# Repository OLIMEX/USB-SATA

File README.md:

# USB-SATA
USB to SATA converter

# License
Hardware is with CERN OHL v1.2 license

Software is with GPL3 license

Documentation is with CC BY-SA 4.0 license

# USB-SATA Benchmark

[Reference](https://www.thomas-krenn.com/en/wiki/Linux_I/O_Performance_Tests_using_dd)

## Commands
### Streaming I/O
    dd if=/dev/zero of=/mnt/testfile bs=1G count=1 oflag=direct
    dd if=/dev/zero of=/mnt/testfile bs=512M count=1 oflag=direct
    dd if=/dev/zero of=/mnt/testfile bs=256M count=1 oflag=direct

### Latency
    hdparm -W0 /dev/sdx
    dd if=/dev/zero of=/mnt/testfile bs=512 count=1000 oflag=direct

## Results

| Board     | Streaming I/O |   Latency  |
| ----------|--------------:| ----------:|
| PC        |     30.2 MB/s | 37.3938 ms |
| A20-MICRO |     28.4 MB/s | 30.5117 ms |
| A10-LIME  |      7.6 MB/s | 33.1223 ms |
| A13-OLXn  |     30.0 MB/s |     -      |
| A64-OLXn  |     31.5 MB/s | 36.6841 ms |

### PC
#### Streaming I/O
    1073741824 bytes (1.1 GB, 1.0 GiB) copied, 35.5515 s, 30.2 MB/s
** 30.2 MB/s **
### Latency
    512000 bytes (512 kB, 500 KiB) copied, 37.3938 s, 13.7 kB/s
** 37.3938 ms **

## A20-OLinuXino-MICRO
### Streaming I/O
    536870912 bytes (537 MB) copied, 18.9142 s, 28.4 MB/s
** 28.4 MB/s **
### Latency
    512000 bytes (512 kB) copied, 30.5117 s, 16.8 kB/s
** 30.5117 ms ** 

## A10-Lime
### Streaming I/O
    268435456 bytes (268 MB) copied, 35.4505 s, 7.6 MB/s
** 7.6 MB/s **
### Latency
    512000 bytes (512 kB) copied, 33.1223 s, 15.5 kB/s
** 33.1223 ms ** 

## A13-OLinuXino
### Streaming I/O
    268435456 bytes (268 MB) copied, 8.96246 s, 30.0 MB/s
** 30.0 MB/s **

## A64-OLinuXino
### Streaming I/O
    536870912 bytes (537 MB, 512 MiB) copied, 17.0416 s, 31.5 MB/s
** 31.5 MB/s **
### Latency
    512000 bytes (512 kB, 500 KiB) copied, 36.6841 s, 14.0 kB/s
** 36.6841 ms **

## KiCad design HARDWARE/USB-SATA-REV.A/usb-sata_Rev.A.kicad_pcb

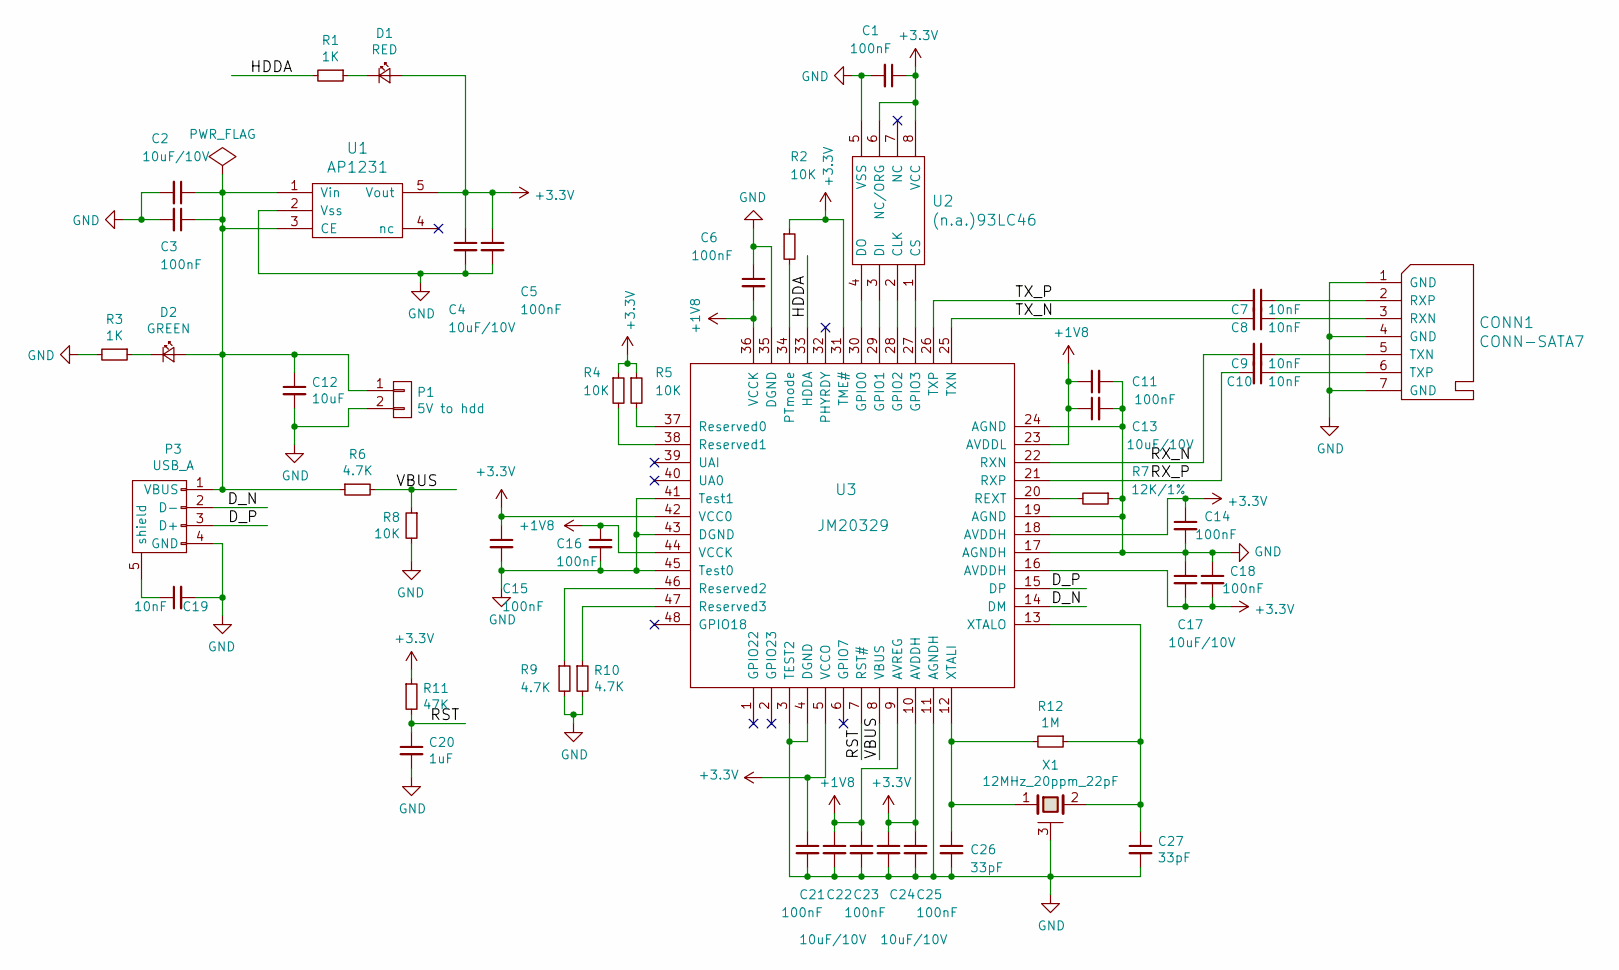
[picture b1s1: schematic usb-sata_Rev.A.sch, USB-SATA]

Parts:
C1, C3, C5, C6, C11, C14, C15, C16, C18, C21, C23, C25: 100nF; C0402
C2, C4, C13, C17, C22, C24: 10uF/10V; C_0603_5MIL_DWS
C7, C8, C9, C10, C19: 10nF; C0402
C12: 10uF; C_0603_5MIL_DWS
C20: 1uF; C0402
C26, C27: 33pF; C0402
CONN1: CONN-SATA7; SATA-MALE-7
D1: RED; LED_0603_KA
D2: GREEN; LED_0603_KA
P1: 5V to hdd; LIPO_BAT-CON2DW02R
P3: USB_A; USB-A-MALE-SMD
R1, R3: 1K; R_0402_5MIL_DWS
R2, R4, R5, R8: 10K; R_0402_5MIL_DWS
R6, R9, R10: 4.7K; R_0402_5MIL_DWS
R7: 12K/1%; R_0402_5MIL_DWS
R11: 47K; R_0402_5MIL_DWS
R12: 1M; R_0402_5MIL_DWS
U1: AP1231; SOT-23-5
U2: (n.a.)93LC46; SOIC-8
U3: JM20329; LQFP48
X1: 12MHz_20ppm_22pF

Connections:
+1V8: C6.2, C11.1, C13.1, C16.1, C22.1, C23.1, U3.9 (AVREG), U3.23 (AVDDL), U3.36 (VCCK), U3.44 (VCCK)
+3V3: C1.1, C4.1, C5.1, C14.1, C15.1, C17.2, C18.2, C21.1, C24.1, C25.1, D1.2 (A), R2.1, R4.1, R5.1, R11.1, U1.5 (Vout), U2.6 (NC/ORG), U2.8 (VCC), U3.5 (VCCO), U3.10 (AVDDH), U3.16 (AVDDH), U3.18 (AVDDH), U3.31 (TME#), U3.42 (VCC0)
/D_N: P3.2 (D-), U3.14 (DM)
/D_P: P3.3 (D+), U3.15 (DP)
/HDDA: R1.2, U3.33 (HDDA)
/RST: C20.1, R11.2, U3.7 (RST#)
/RX_N: C9.2, U3.22 (RXN)
/RX_P: C10.2, U3.21 (RXP)
/TX_N: C8.2, U3.25 (TXN)
/TX_P: C7.2, U3.26 (TXP)
/VBUS: R6.2, R8.1, U3.8 (VBUS)
GND: C1.2, C2.2, C3.2, C4.2, C5.2, C6.1, C11.2, C12.2, C13.2, C14.2, C15.2, C16.2, C17.1, C18.1, C19.2, C20.2, C21.2, C22.2, C23.2, C24.2, C25.2, C26.2, C27.2, CONN1.1 (GND), CONN1.4 (GND), CONN1.7 (GND), P1.2, P3.4 (GND), R3.2, R7.1, R8.2, R9.2, R10.2, U1.2 (Vss), U2.5 (VSS), U3.3 (TEST2), U3.4 (DGND), U3.11 (AGNDH), U3.17 (AGNDH), U3.19 (AGND), U3.24 (AGND), U3.35 (DGND), U3.41 (Test1), U3.43 (DGND), U3.45 (Test0), X1.3 (case)
unnamed: C7.1, CONN1.2 (RXP)
unnamed: C8.1, CONN1.3 (RXN)
unnamed: C9.1, CONN1.5 (TXN)
unnamed: C10.1, CONN1.6 (TXP)
unnamed: C2.1, C3.1, C12.1, D2.2 (A), P1.1, P3.1 (VBUS), R6.1, U1.1 (Vin), U1.3 (CE)
unnamed: C19.1, P3.5 (shield)
unnamed: C26.1, R12.2, U3.12 (XTALI), X1.1
unnamed: C27.1, R12.1, U3.13 (XTALO), X1.2
unnamed: D1.1 (K), R1.1
unnamed: D2.1 (K), R3.1
unnamed: R2.2, U3.34 (PTmode)
unnamed: R4.2, U3.38 (Reserved1)
unnamed: R5.2, U3.37 (Reserved0)
unnamed: R7.2, U3.20 (REXT)
unnamed: R9.1, U3.46 (Reserved2)
unnamed: R10.1, U3.47 (Reserved3)
unnamed: U2.1 (CS), U3.27 (GPIO3)
unnamed: U2.2 (CLK), U3.28 (GPIO2)
unnamed: U2.3 (DI), U3.29 (GPIO1)
unnamed: U2.4 (DO), U3.30 (GPIO0)

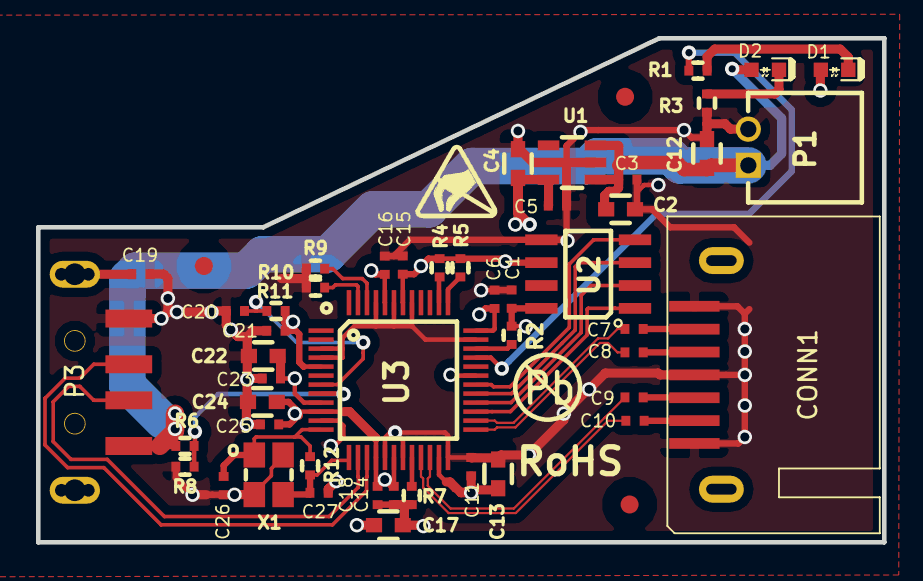
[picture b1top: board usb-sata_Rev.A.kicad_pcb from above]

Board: 4 copper layers, 47.0 x 28.0 mm, 49 parts (0 on the bottom side), 32 nets.

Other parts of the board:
Ref**: Val**; LOGO_ANTISTATIC_SMALL_4.5mmX2.8mm

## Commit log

2019-07-17 Initial upload
